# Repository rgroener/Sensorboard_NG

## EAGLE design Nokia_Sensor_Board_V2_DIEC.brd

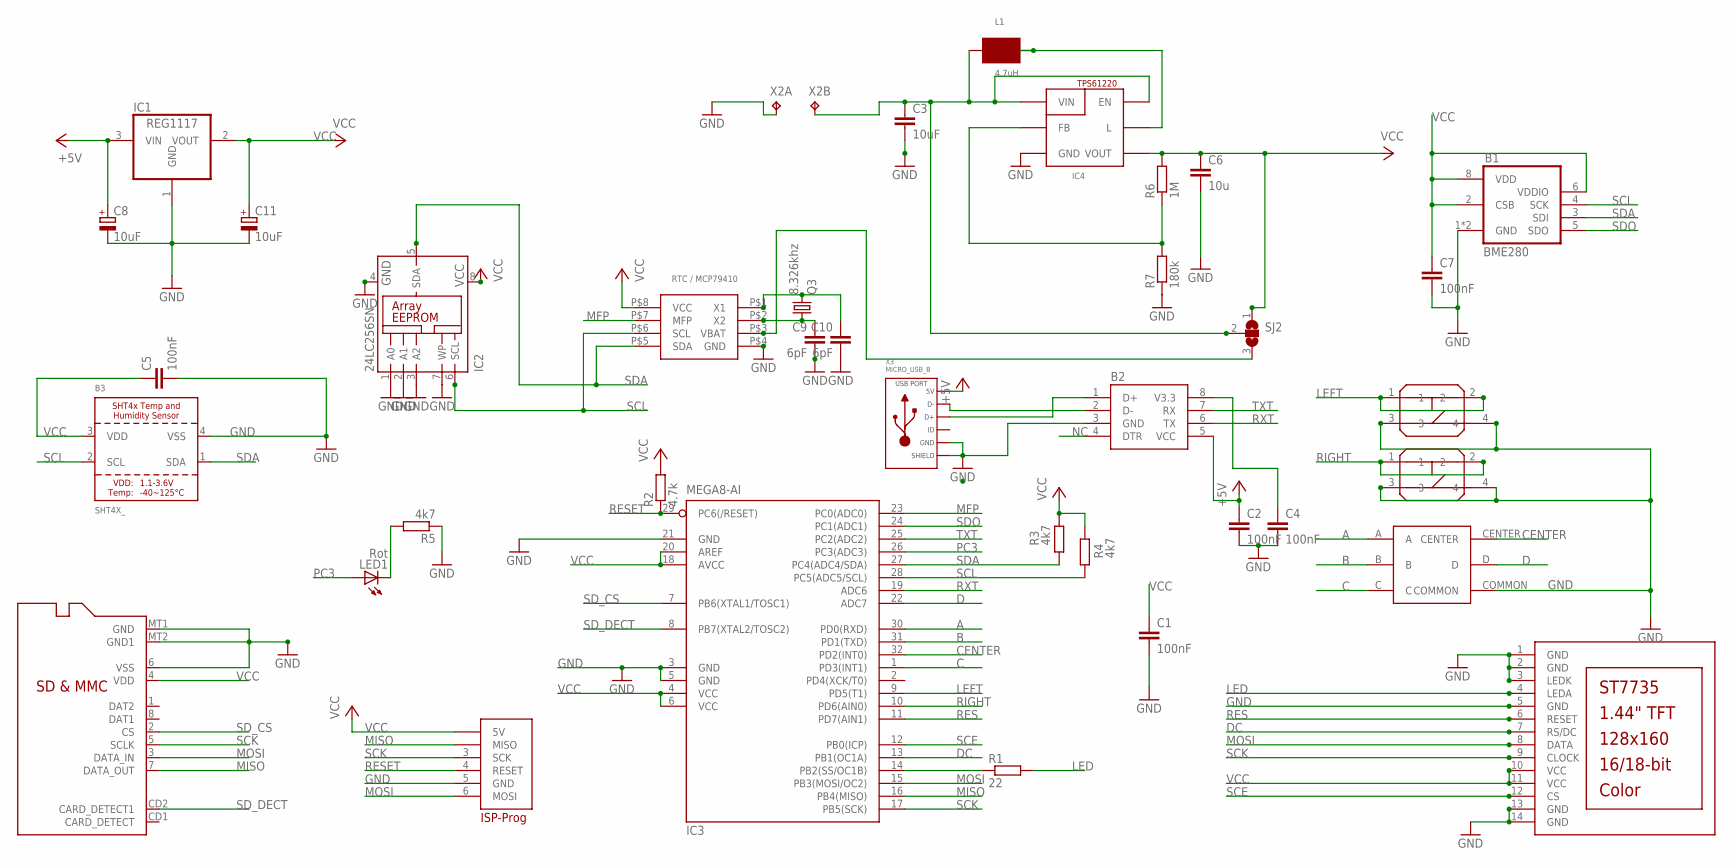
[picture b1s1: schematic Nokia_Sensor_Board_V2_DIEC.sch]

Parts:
B1: BME280
B2: CH330N; SOIC8
B3: SHT4X_; SHT4X
C1, C2, C4, C5, C7: 100nF; C0805
C3: 10uF; C0805
C6: 10u; C0805
C8, C11: 10uF; SMC_A
C9, C10: 6pF; C0805
C12: MICROSD
IC1: REG1117; SOT223
IC2: 24LC256SN; SO-08
IC3: MEGA8-AI; TQFP32-08
IC4: TPS6122X
L1: 4.7uH; SPULE_SMD
LED1: Rot; SML0805
P1: DISP_LCD_ST7735_1.44IN; TFT_1.44IN_128_128
P2: MCP79410
Q3: 8.326khz; TC38H
R1: 22; M0805
R2: 4.7k; M0805
R3, R4, R5: 4k7; M0805
R6: 1M; R0805
R7: 180k; R0805
S1, S3: TASTER_GROSS
S2: SKQUCAA010
SJ2: SJ2W; SJ_2
X1: ISP_PROG_STECKERJST-PH6; ISP_PROG_JST_PH6
X2: TP2P2-38-17; P2-38-17
X3: MICRO_USB_B

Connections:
+5V: B2.5 (VCC), C2.1, C8.+, IC1.3 (VIN), X3.1 (5V)
A: IC3.30 (PD0(RXD)), S2.A
B: IC3.31 (PD1(TXD)), S2.B
C: IC3.1 (PD3(INT1)), S2.C
CENTER: IC3.32 (PD2(INT0)), S2.CENTER
D: IC3.22 (ADC7), S2.D
D+: B2.1 (D+), X3.3 (D+)
D-: B2.2 (D-), X3.2 (D-)
DC: IC3.13 (PB1(OC1A)), P1.7 (RS/DC)
GND: B1.1 (GND), B1.7 (GND), B2.3 (GND), B3.4 (VSS), C1.2, C2.2, C3.2, C4.2, C5.2, C6.2, C7.2, C8.-, C9.2, C10.2, C11.-, C12.6 (VSS), C12.MT1 (GND), C12.MT2 (GND1), IC1.1 (GND), IC2.1 (A0), IC2.2 (A1), IC2.3 (A2), IC2.4 (GND), IC2.7 (WP), IC3.3 (GND), IC3.5 (GND), IC3.21 (GND), IC4.P$3 (GND), P1.1 (GND), P1.2 (GND), P1.3 (LEDK), P1.5 (GND), P1.13 (GND), P1.14 (GND), P2.P$4 (GND), R5.1, R7.1, S1.3, S1.4, S2.COMMON, S3.3, S3.4, X1.5 (GND), X2.TP-1, X3.5 (GND), X3.S1 (SLD), X3.S2 (SLD), X3.S5 (SLD), X3.S6 (SLD), X3.S7 (SLD), X3.S8 (SLD)
LED: P1.4 (LEDA), R1.2
LEFT: IC3.9 (PD5(T1)), S1.1, S1.2
MFP: IC3.23 (PC0(ADC0)), P2.P$7 (MFP)
MISO: C12.7 (DATA_OUT), IC3.16 (PB4(MISO)), X1.2 (MISO)
MOSI: C12.3 (DATA_IN), IC3.15 (PB3(MOSI/OC2)), P1.8 (DATA), X1.6 (MOSI)
unnamed: P2.P$3 (VBAT), SJ2.3
unnamed: LED1.C, R5.2
unnamed: B2.8 (V3.3), C4.1
unnamed: IC3.14 (PB2(SS/OC1B)), R1.1
unnamed: IC4.P$2 (FB), R6.1, R7.2
unnamed: C3.1, IC4.P$1 (VIN), IC4.P$6 (EN), L1.P$2 (.), SJ2.2, X2.TP-2
unnamed: IC4.P$5 (L), L1.P$1 (-)
unnamed: C9.1, P2.P$2 (X2), Q3.1
unnamed: C10.1, P2.P$1 (X1), Q3.2
NC: B2.4 (DTR)
PC3: IC3.26 (PC3(ADC3)), LED1.A
RES: IC3.11 (PD7(AIN1)), P1.6 (RESET)
RESET: IC3.29 (PC6(/RESET)), R2.1, X1.4 (RESET)
RIGHT: IC3.10 (PD6(AIN0)), S3.1, S3.2
RXT: B2.6 (TX), IC3.19 (ADC6)
SCE: IC3.12 (PB0(ICP)), P1.12 (CS)
SCK: C12.5 (SCLK), IC3.17 (PB5(SCK)), P1.9 (CLOCK), X1.3 (SCK)
SCL: B1.4 (SCK), B3.2 (SCL), IC2.6 (SCL), IC3.28 (PC5(ADC5/SCL)), P2.P$6 (SCL), R4.1
SDA: B1.3 (SDI), B3.1 (SDA), IC2.5 (SDA), IC3.27 (PC4(ADC4/SDA)), P2.P$5 (SDA), R3.1
SDO: B1.5 (SDO), IC3.24 (PC1(ADC1))
SD_CS: C12.2 (CS), IC3.7 (PB6(XTAL1/TOSC1))
SD_DECT: C12.CD2 (CARD_DETECT1), IC3.8 (PB7(XTAL2/TOSC2))
TXT: B2.7 (RX), IC3.25 (PC2(ADC2))
VCC: B1.2 (CSB), B1.6 (VDDIO), B1.8 (VDD), B3.3 (VDD), C1.1, C5.1, C6.1, C7.1, C11.+, C12.4 (VDD), IC1.2 (VOUT), IC2.8 (VCC), IC3.4 (VCC), IC3.6 (VCC), IC3.18 (AVCC), IC3.20 (AREF), IC4.P$4 (VOUT), P1.10 (VCC), P1.11 (VCC), P2.P$8 (VCC), R2.2, R3.2, R4.2, R6.2, SJ2.1, X1.1 (5V)

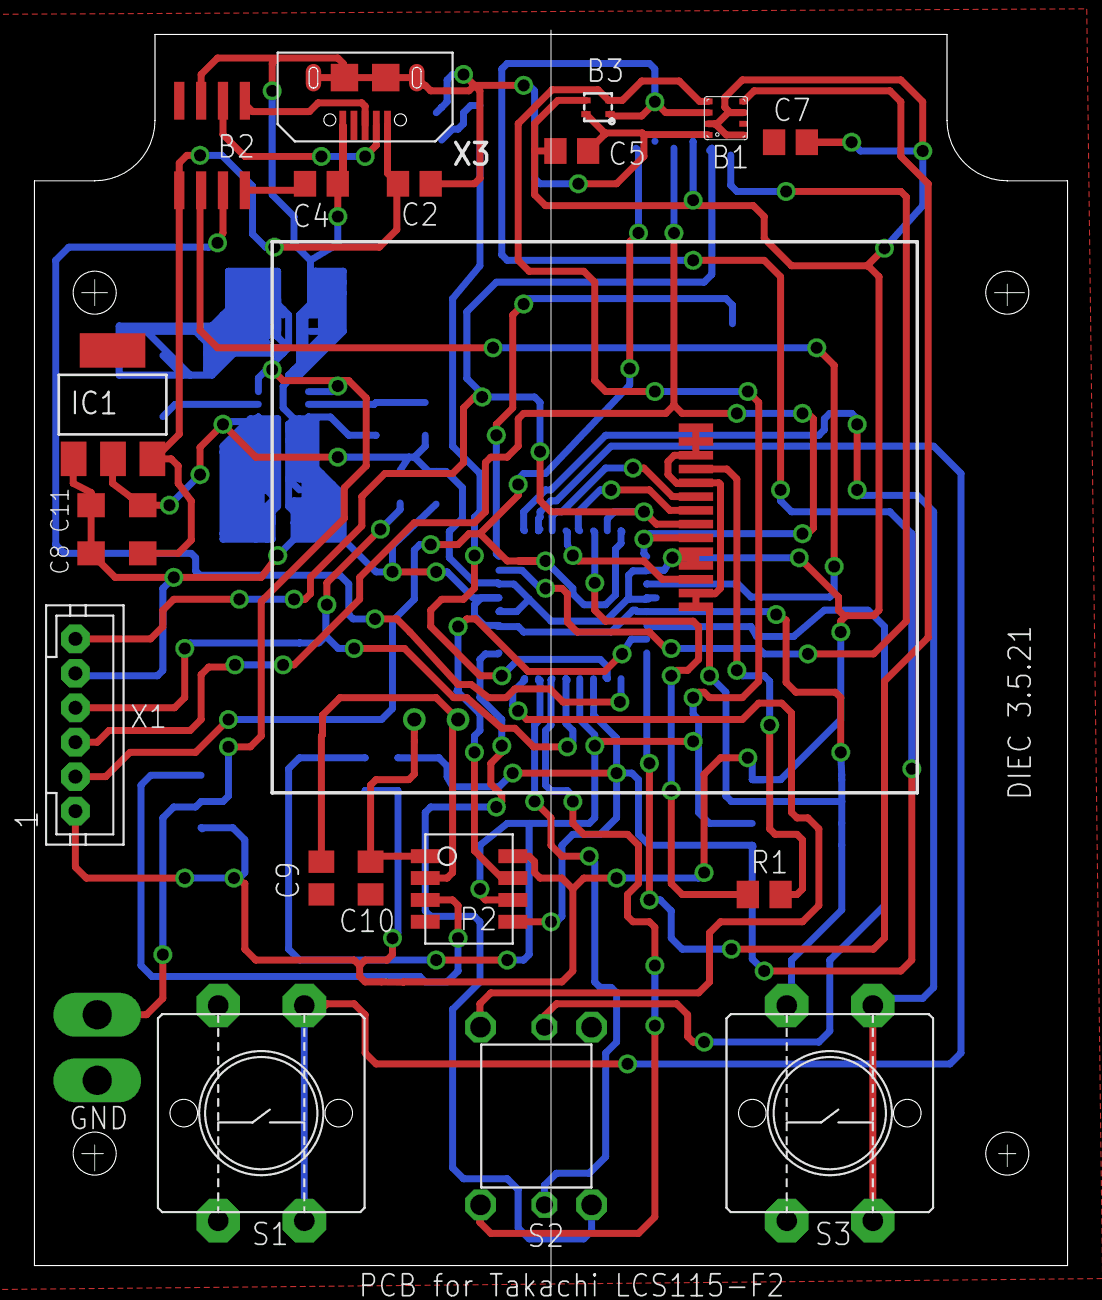
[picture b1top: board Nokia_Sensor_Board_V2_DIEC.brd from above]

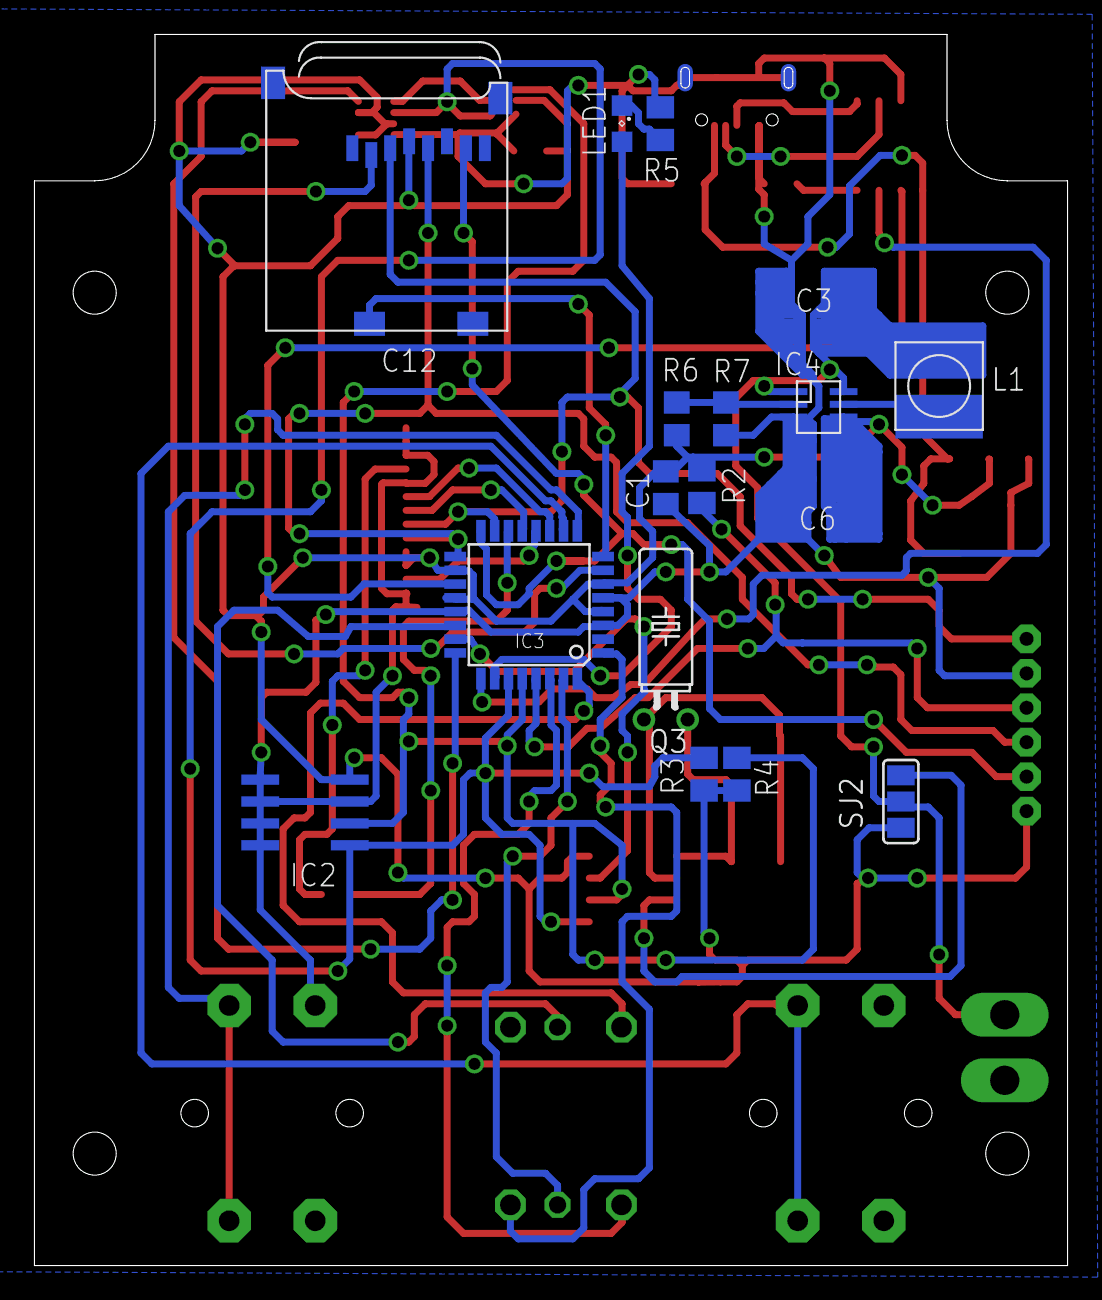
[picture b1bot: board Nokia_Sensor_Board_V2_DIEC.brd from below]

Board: 2 copper layers, 60.0 x 71.5 mm, 39 parts (17 on the bottom side), 38 nets.

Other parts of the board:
U$1: PCB_LSC115_F2

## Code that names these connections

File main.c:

/* 
 * Sonsorboard New Generation
 * GRN / Mai 2022
 * 
 * 
*/

#define F_CPU 8000000UL                 // set the CPU clock
#include <avr/io.h>
#include <avr/interrupt.h>
#include <stdio.h>
#include <stdlib.h>
#include <avr/pgmspace.h>
#include <util/delay.h>
#include "st7735.h"
#include "grn_TWI.h"
#include "EEPROM_64.h"
#include "spi.h"


#define BACKLIGHT_ON PORTB |= (1<<PB2)
#define BACKLIGHT_OFF PORTB &= ~(1<<PB2)						

#define LED_OFF PORTC &= ~(1<<PC3)
#define LED_ON PORTC |= (1<<PC3)

#define USART_BAUDRATE 9600
#define BAUD_PRESCALE (((F_CPU / (USART_BAUDRATE * 16UL)))-1)
//Buttons 


/* some RGB color definitions                                                 */
#define BLACK        0x0000      
#define RED          0x001F      
#define GREEN        0x07E0      
#define YELLOW       0x07FF      
#define BLUE         0xF800      
#define CYAN         0xFFE0      
#define White        0xFFFF     
#define BLUE_LIGHT   0xFD20      
#define TUERKISE     0xAFE5      
#define VIOLET       0xF81F		
#define WHITE		0xFFFF

#define SEK_POS 10,110

#define RELOAD_ENTPRELL 1 


#define TW_START 0xA4 // send start condition (TWINT,TWSTA,TWEN)
#define TW_READY (TWCR & 0x80) // ready when TWINT returns to logic 1.
#define TW_STATUS (TWSR & 0xF8) // returns value of status register
#define TW_SEND 0x84 // send data (TWINT,TWEN)

#define 	B_BLUE		!(PIND & (1<<PD6))
#define 	B_GREEN		!(PIND & (1<<PD2))
#define	B_YELLOW	!(PIND & (1<<PD5))

#define F_SCL 100000L // I2C clock speed 100 kHz
//#define F_CPU 800000L // I2C clock speed 100 kHz


// Pins already defined in st7735.c
extern int const DC;
extern int const MOSI;
extern int const SCK;
extern int const CS;
// Text scale and plot colours defined in st7735.c
extern int fore; 		// foreground colour
extern int back;      	// background colour
extern int scale;     	// Text size


volatile uint8_t ms10,ms100,sec,min, entprell;
volatile uint16_t speedtest, speedflag;

char stringbuffer[20]; // buffer to store string 
uint8_t addresse, position;//test twi ausgabe

ISR (TIMER1_COMPA_vect);
void twi_Init(void);
void twi_Start(void);
void twi_Stop(void);
void twi_Write(uint8_t u8data);
uint8_t twi_GetStatus(void);




//UART
void uart_send_char(char c);
void uart_send_string(volatile char *s);
ISR(USART0_RX_vect);

int main(void)
{
	DDRB |= (1<<DC) | (1<<CS) | (1<<MOSI) |( 1<<SCK); 	// All outputs
	PORTB = (1<<SCK) | (1<<CS) | (1<<DC);          		// clk, dc, and cs high
	DDRB |= (1<<PB2);									//lcd Backlight output
	PORTB |= (1<<CS) | (1<<PB2);                  		// cs high
	DDRC |= (1<<PC3);									//Reset Output
	DDRD |= (1<<PD7);									//Reset Output
	PORTD |= (1<<PD7);	
									//Reset High
	DDRD &= ~((1<<PD6) | (1<<PD2) | (1<<PD5)); 	//Taster 1-3
	PORTD |= ((1<<PD6) | (1<<PD2) | (1<<PD5)); 	//PUllups für Taster einschalten
	
	DDRD |= (1<<PD1)| (1<<PD0);//set TX0 as output
	DDRD &= ~(1<<PD0);//set Rx as Input
	//Timer 1 Configuration
	OCR1A = 1249;	//OCR1A = 0x3D08;==1sec
	    TCCR1B |= (1 << WGM12);
    // Mode 4, CTC on OCR1A
    TIMSK1 |= (1 << OCIE1A);
    //Set interrupt on compare match
    TCCR1B |= (1 << CS11) | (1 << CS10);
    // set prescaler to 64 and start the timer
    /* Enable SPI, Master, set clock rate fck/2 */
	SPCR = (1<<SPE)|(1<<MSTR); 
	SPSR = (1<<SPI2X);
	
	//UART0
    UCSR0B = (1<<RXEN0) | (1<<TXEN0) | (1<<RXCIE0);	//Turn on RX and TX circuits RXCIE0 enables Interrupt when byte received
	UCSR0C = (1<<UCSZ01) | (1<<UCSZ00);	//8-Bit Char size
	UBRR0H = (BAUD_PRESCALE >> 8);	//load upper 8-Bits of baud rate value into high byte of UBRR0H
	UBRR0L = BAUD_PRESCALE;			//load lower 8-Bits of Baud rate into low byte of UBRR0L
	
    sei();// enable interrupts
    
    ms10=0;
    ms100=0;
    sec=0;
    min=0;
    entprell=0;
	
	BACKLIGHT_ON;
	LED_ON;

	setup();
	//SPI_MasterInit();
	TWIInit();

	addresse=0;
	position=20;
		
	fore = WHITE; // White
	scale = 1;//font size
	
	speedtest=0;
	speedflag=1;
	
	MoveTo(0,80);
	fore = WHITE;//set color
	FillRect(40,40);
	
	fore = YELLOW;//set color
	uart_send_string("Hello\n\r");
	speedflag=0; // Stop speedcounter
	
	MoveTo(10,0);
	scale=2;
	sprintf(stringbuffer,"ms = %d",speedtest);
	PlotString(stringbuffer);
	
	fore=WHITE;
	/*MoveTo(10,10);
	sprintf(stringbuffer,"r:%d",234);
	PlotString(stringbuffer);*/
	scale=2;
	  for (;;)
	  {
			
			
			if(B_BLUE)sec++;
			if(B_GREEN)sec--;
			if(B_YELLOW)sec=0;
			
							
		}//end of for()
}//end of main

ISR (TIMER1_COMPA_vect)
{
	ms10++;
	
	if(speedflag==1)speedtest++;
			
	if(ms10==10)	//10ms
	{
		ms10=0;
		ms100++;
	}
    if(ms100==10)	//100ms
	{
		ms100=0;
		sec++;
	}
	if(sec==60)	//Minute
	{
		sec=0;
		min++;
	}
}

void uart_send_char(char c)
{
	while((UCSR0A & (1<<UDRE0)) == 0){};
    UDR0 = c;
}
void uart_send_string(volatile char *s)
{
	while(*s != 0x00)
	{
		uart_send_char(*s);
		s++;
	}
}//end of send_string

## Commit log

2022-05-15 added uart blind=> to be tested
2022-05-15 added libraries => to be tested

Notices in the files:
parts and their libraries:
microbuilder: This work is placed in the public domain, and may be freely used for commercial and non-commercial work with the following conditions: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
